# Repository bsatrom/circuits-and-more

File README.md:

# circuits-and-more
Repository for Milling projects (PCBs, materials, etc.)

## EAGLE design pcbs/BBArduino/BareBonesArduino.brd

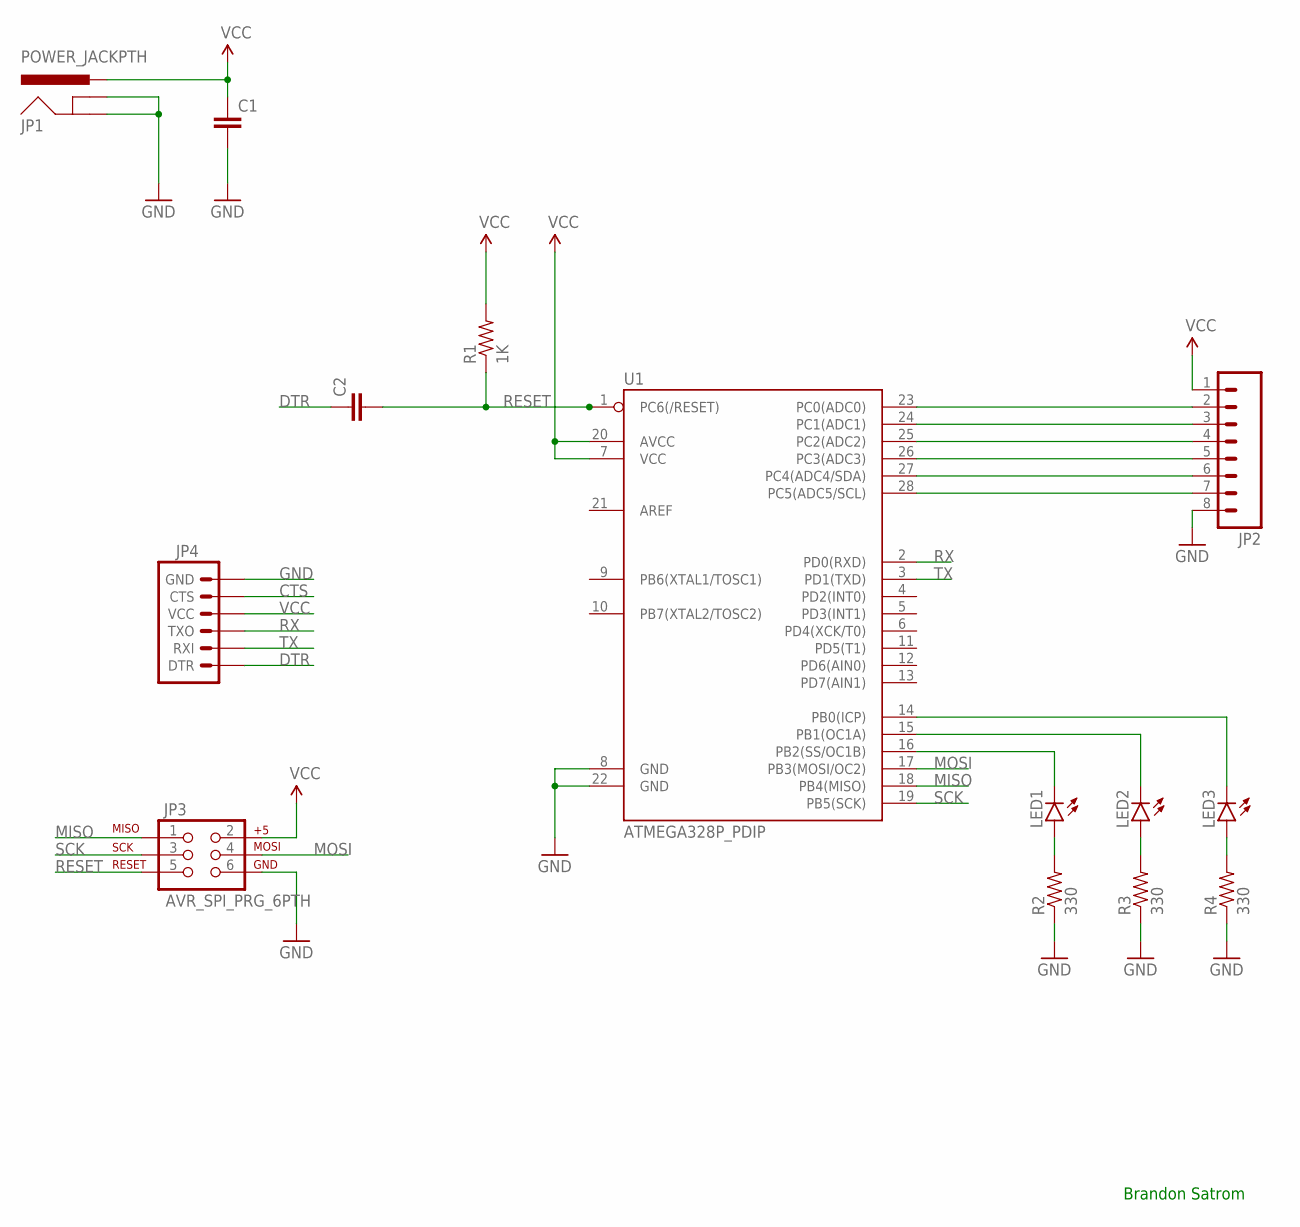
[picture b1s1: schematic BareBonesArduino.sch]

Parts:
C1, C2: CAPPTH; CAP-PTH-SMALL
JP1: POWER_JACKPTH; POWER_JACK_PTH
JP2: M08; 1X08_ROUND
JP3: AVR_SPI_PRG_6PTH; 2X3
JP4: ARDUINO_SERIAL_PROGRAMPTH; 1X06
LED1, LED2, LED3: LED5MM
R1: 1K; AXIAL-0.4
R2, R3, R4: 330; AXIAL-0.4
U1: ATMEGA328P_PDIP; DIL28-3

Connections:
CTS: JP4.5 (CTS)
DTR: C2.1, JP4.1 (DTR)
GND: C1.2, JP1.GND, JP1.GNDBREAK, JP2.8, JP3.6, JP4.6 (GND), R2.P$1 (1), R3.P$1 (1), R4.P$1 (1), U1.8 (GND), U1.22 (GND)
MISO: JP3.1, U1.18 (PB4(MISO))
MOSI: JP3.4, U1.17 (PB3(MOSI/OC2))
unnamed: JP2.2, U1.23 (PC0(ADC0))
unnamed: JP2.3, U1.24 (PC1(ADC1))
unnamed: JP2.4, U1.25 (PC2(ADC2))
unnamed: JP2.5, U1.26 (PC3(ADC3))
unnamed: JP2.6, U1.27 (PC4(ADC4/SDA))
unnamed: JP2.7, U1.28 (PC5(ADC5/SCL))
unnamed: LED3.K (C), U1.14 (PB0(ICP))
unnamed: LED3.A, R4.P$2 (2)
unnamed: LED2.A, R3.P$2 (2)
unnamed: LED1.A, R2.P$2 (2)
unnamed: LED2.K (C), U1.15 (PB1(OC1A))
unnamed: LED1.K (C), U1.16 (PB2(SS/OC1B))
RESET: C2.2, JP3.5, R1.P$1 (1), U1.1 (PC6(/RESET))
RX: JP4.3 (TXO), U1.2 (PD0(RXD))
SCK: JP3.3, U1.19 (PB5(SCK))
TX: JP4.2 (RXI), U1.3 (PD1(TXD))
VCC: C1.1, JP1.PWR, JP2.1, JP3.2, JP4.4 (VCC), R1.P$2 (2), U1.7 (VCC), U1.20 (AVCC)

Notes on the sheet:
Brandon Satrom

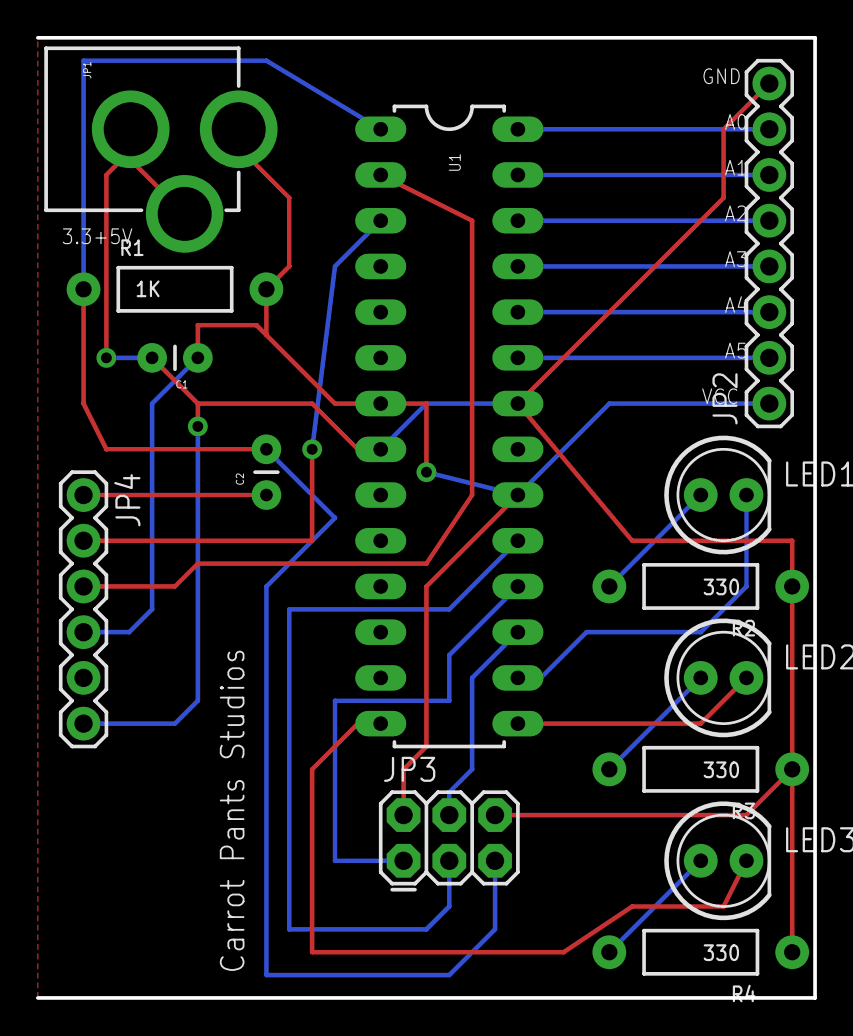
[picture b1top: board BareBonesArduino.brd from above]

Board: 2 copper layers, 43.2 x 53.3 mm, 14 parts (0 on the bottom side), 21 nets.

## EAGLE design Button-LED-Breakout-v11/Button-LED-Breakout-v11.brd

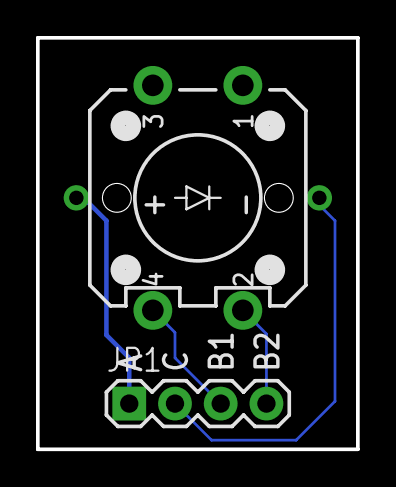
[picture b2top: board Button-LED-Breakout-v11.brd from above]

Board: 2 copper layers, 17.8 x 22.9 mm, 4 parts (1 on the bottom side), 4 nets.

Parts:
JP1: 1X04
JP2: LOGO-SFESK; SFE-LOGO-FLAME
S1: SWITCH-MOMENTARY-LEDPTH; TACTILE-PTH-LED-12MM
U$2: CREATIVE_COMMONS

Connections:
unnamed: JP1.4, S1.2
unnamed: JP1.3, S1.4
unnamed: JP1.2, S1.A
unnamed: JP1.1, S1.C

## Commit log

2015-06-04 modified .gitignore
2015-06-04 completed BBArduino board
2015-06-17 adding new engraving projects
2016-06-24 long-overdue update
2016-07-11 added cam job for stacking rings
2016-07-12 adjusted stacking ring cam for stock size
2016-07-12 updated brewbuddy eagle components
2016-07-22 added ebony ring cam file
2016-07-25 fixed facing positioning
2016-08-29 added gopro files;
2016-08-30 added lulzbot parts
2016-09-26 added stacking rings design
2016-09-28 updated Alumnium ring gcode
2016-11-19 added svg for dog tag design
2017-01-12 added percy
2017-07-08 add bike mount files
2017-07-16 cps logos
2017-10-08 added B&J ring
2018-02-15 modified brass ring
2018-03-03 added lamp shade stls
2018-03-04 added st-microelectronics
2018-03-17 added pegboard print files
2018-03-18 added lulzbot cold pull files
2018-03-24 added ellie gerbers
2018-04-14 updated gerbers for othermill
2018-04-14 updated gerbers for Ellie board
2018-04-14 update ellie pcb for othermill
2018-04-14 edit ellie gerbers to be othermill compatible
2018-05-04 added MF resources
2018-05-08 added SpaceTeam Logo
2018-05-11 added modified breakout for LED button

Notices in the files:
parts and their libraries:
SparkFun: Released under the Creative Commons Attribution Share-Alike 3.0 License
SparkFun: http://creativecommons.org/licenses/by-sa/3.0
SparkFun-Capacitors: Licensing: Creative Commons ShareAlike 4.0 International - https://creativecommons.org/licenses/by-sa/4.0
